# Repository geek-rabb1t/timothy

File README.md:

# Timothy

使いやすさを追求した左右分離型の自作キーボードキットです。
3Dプリント品のケースを採用することで市販品のような形状を実現しています。

キーボードキットや、半完成品は以下のサイトで販売しています。
カスタマイズしたり、ご自身で発注したい場合はこのリポジトリデータをご利用ください。

- キーボードキット：  
https://geek-rabb1t.booth.pm/items/4213539
- パームレスト：  
https://geek-rabb1t.booth.pm/items/4214631

## ディレクトリ構成

* case  
caseの3Dデータ
* doc  
ビルドガイド
* firmware  
ビルド済みのファームウェアや、各種設定データ
* gasket  
ガスケットのカッティングデータ
* palm-rest  
パームレストトップのカッティングデータ
* pcb
PCBのデータ
* plate  
スイッチプレートの外形データ

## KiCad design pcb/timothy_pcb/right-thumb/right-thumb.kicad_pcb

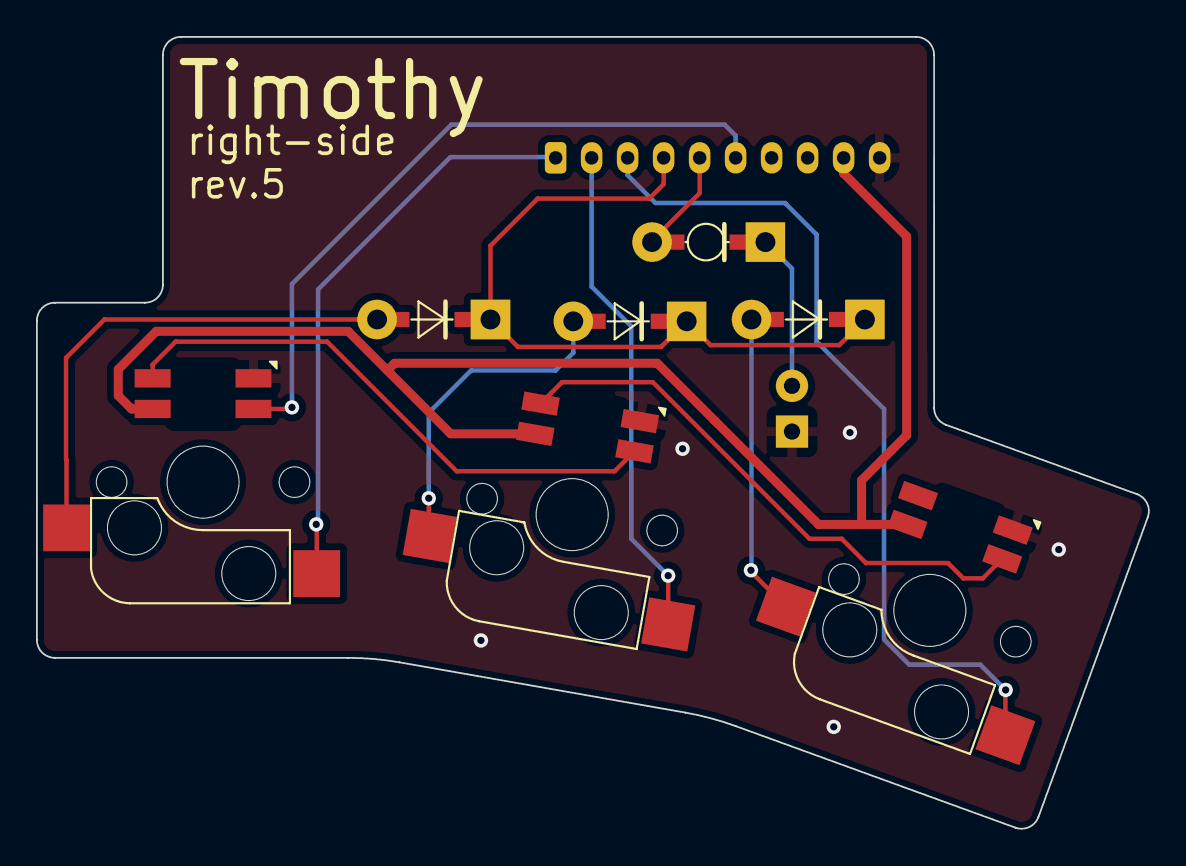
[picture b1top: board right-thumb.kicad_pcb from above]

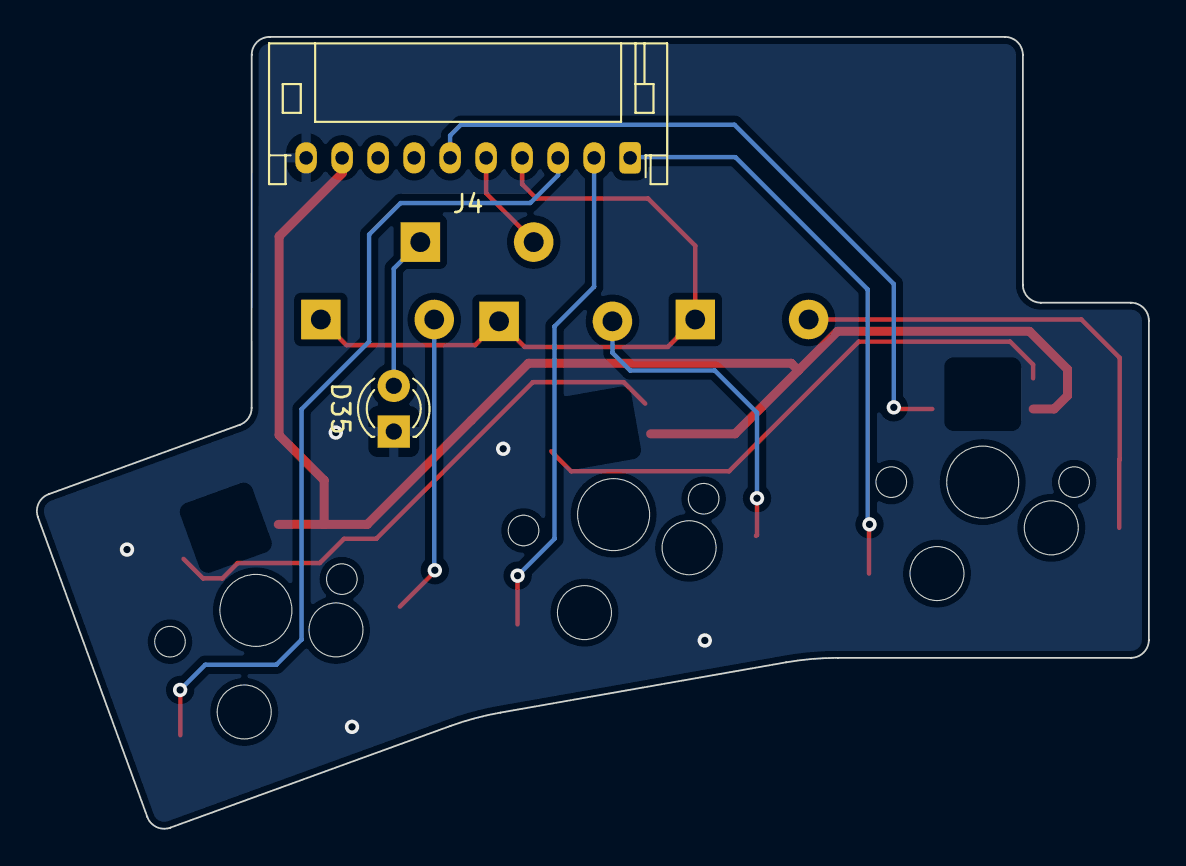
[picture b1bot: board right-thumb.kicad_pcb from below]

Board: 2 copper layers, 61.8 x 44.0 mm, 9 parts (2 on the bottom side), 14 nets.

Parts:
D35: LED; LED_D3.0mm
D36: CRD
D81, D82, D83: D; Diode
J4: Conn_01x10; JST_PH_S10B-PH-K_1x10_P2.00mm_Horizontal
SW68, SW69, SW70: Key_Switch_with_LED; MX_Socket_LED

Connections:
/BACKLIGHT_IN: J4.6, SW70.6 (DIN)
/C4: J4.1, SW70.1
/C5: J4.2, SW69.1
/C6: J4.3, SW68.1
/PWR_LED: D36.2 (A), J4.5
/R5: D81.1 (K), D82.1 (K), D83.1 (K), J4.4
/VCC: J4.9, SW68.3 (VDD), SW69.3 (VDD), SW70.3 (VDD)
GND: D35.1 (K), J4.10, SW68.5 (GND), SW69.5 (GND), SW70.5 (GND)
unnamed: D35.2 (A), D36.1 (K)
unnamed: D81.2 (A), SW68.2
unnamed: D82.2 (A), SW69.2
unnamed: D83.2 (A), SW70.2
unnamed: SW68.6 (DIN), SW69.4 (DOUT)
unnamed: SW69.6 (DIN), SW70.4 (DOUT)

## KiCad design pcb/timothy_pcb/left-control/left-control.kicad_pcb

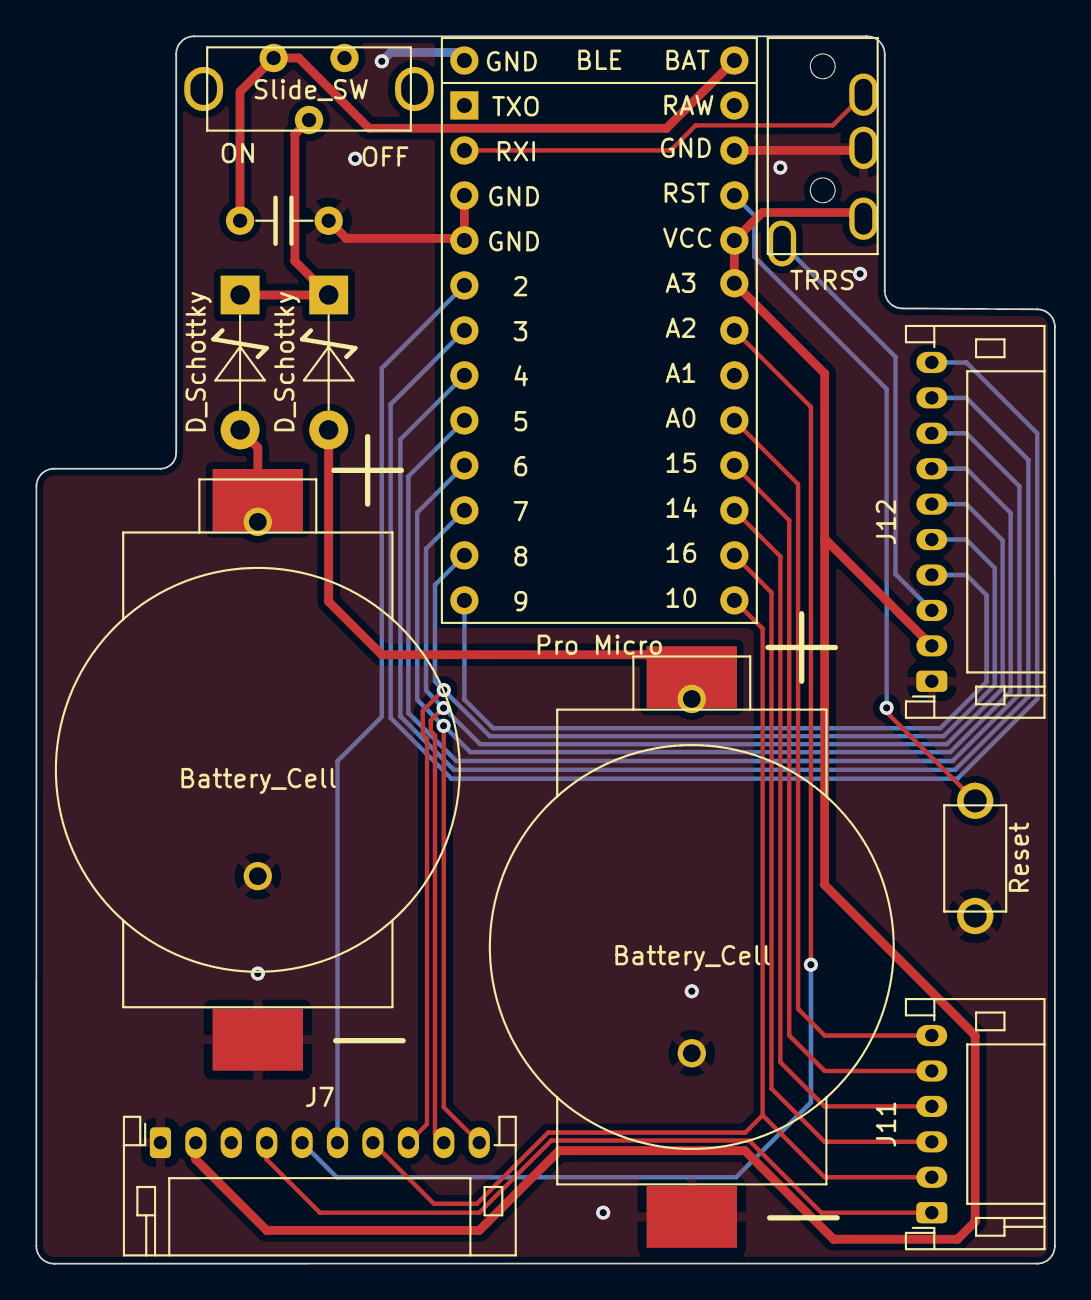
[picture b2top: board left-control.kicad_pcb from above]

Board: 2 copper layers, 57.5 x 69.3 mm, 12 parts (0 on the bottom side), 24 nets.

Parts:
BT1, BT2: Battery_Cell; CR2032_Holder_SMD
C1: 100μF; Capacitor
D70, D71: D_Schottky; Shottky_Barrier_Diode
J5: TRRS
J7: to_thumb; JST_PH_S10B-PH-K_1x10_P2.00mm_Horizontal
J11: control_to_main_1; JST_PH_S6B-PH-K_1x06_P2.00mm_Horizontal
J12: control_to_main_2; JST_PH_S10B-PH-K_1x10_P2.00mm_Horizontal
SW31: Slide_SW; Slide_Switch_ESD175202
SW63: Reset; Tactile_Switch
U1: Pro Micro; BLE_Micro_Pro

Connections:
/left_control/BACKLIGHT_TO_RIGHT: J5.4, J12.3
/left_control/BAT: C1.1, SW31.2 (B), U1.25 (BAT)
/left_control/C1: J12.10, U1.6 (PIN6)
/left_control/C2: J12.9, U1.7 (PIN7)
/left_control/C3: J12.8, U1.8 (PIN8)
/left_control/C4: J7.10, J12.7, U1.9 (PIN9)
/left_control/C5: J7.9, J12.6, U1.10 (PIN10)
/left_control/C6: J7.8, J12.5, U1.11 (PIN11)
/left_control/C7: J12.4, U1.12 (PIN12)
/left_control/FROM_THUMB_BACKLIGHT: J7.4, J11.1
/left_control/PWR_LED: J7.6, U1.5 (PIN5)
/left_control/R1: J11.6, U1.17 (PIN17)
/left_control/R2: J11.5, U1.16 (PIN16)
/left_control/R3: J11.4, U1.15 (PIN15)
/left_control/R4: J11.3, U1.14 (PIN14)
/left_control/R5: J7.7, J11.2, U1.13 (PIN13)
/left_control/SERIAL: J5.1, U1.2 (PIN2)
/left_control/TO_THUMB_BACKLIGHT: J7.5, U1.19 (PIN19)
/left_control/VCC: J5.3, J7.2, J12.2, U1.20 (PIN20), U1.21 (+4.3V)
GND: BT1.2 (-), BT2.2 (-), C1.2, J5.2, J7.1, J12.1, SW63.1, U1.0 (GND), U1.3 (GND), U1.4 (GND), U1.23 (GND)
unnamed: BT1.1 (+), D70.2 (A)
unnamed: BT2.1 (+), D71.2 (A)
unnamed: D70.1 (K), D71.1 (K), SW31.1 (A)
unnamed: SW63.2, U1.22 (BOOT(RST))

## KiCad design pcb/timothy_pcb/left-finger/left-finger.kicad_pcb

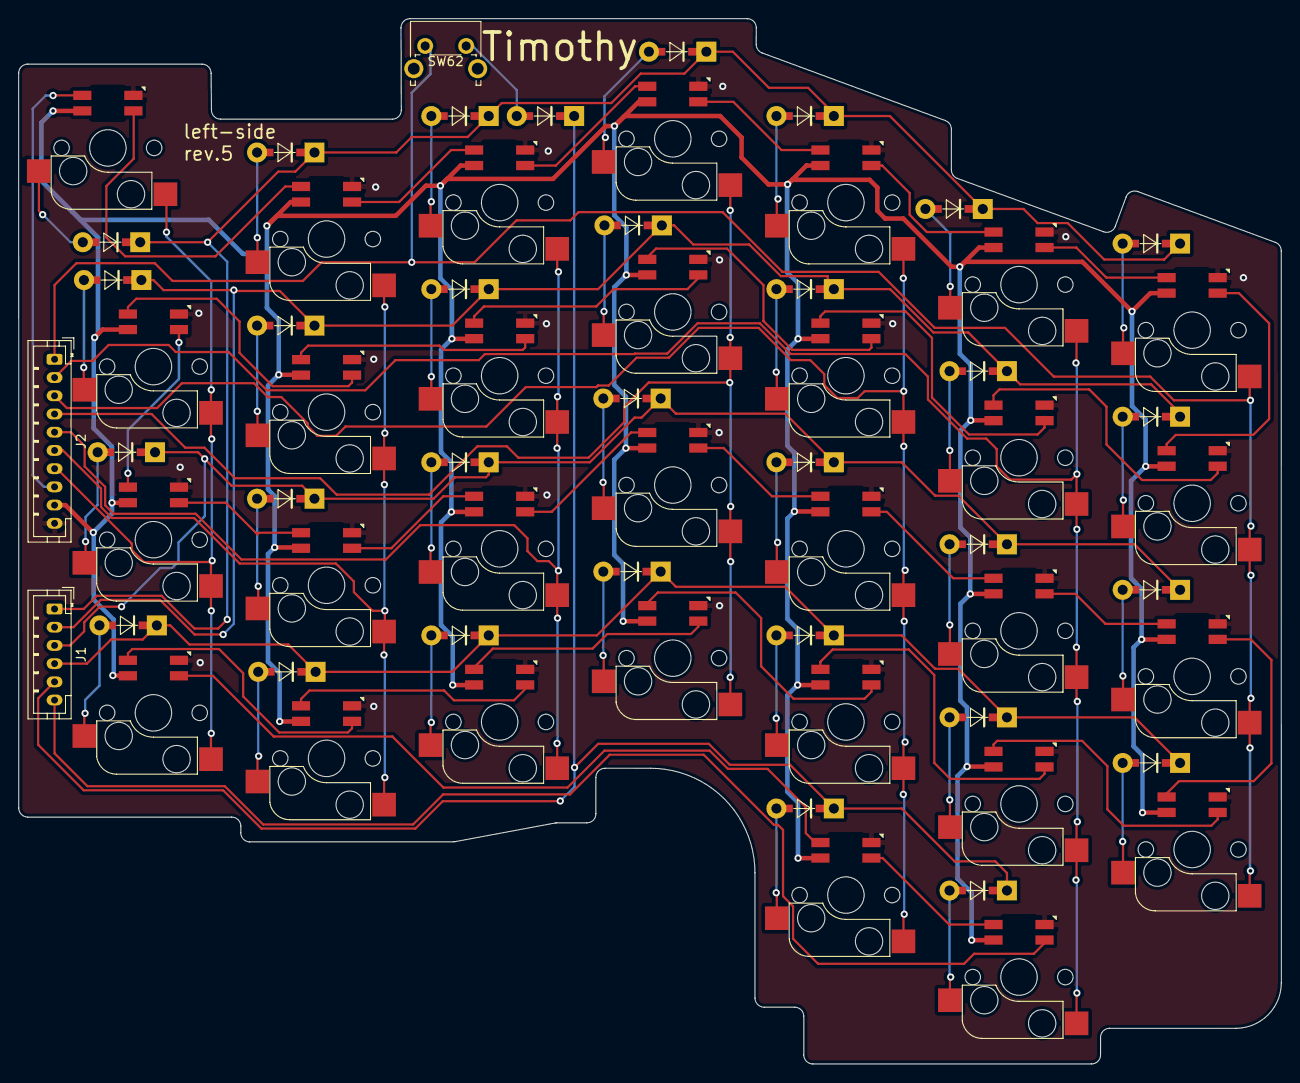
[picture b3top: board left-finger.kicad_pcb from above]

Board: 2 copper layers, 138.6 x 114.7 mm, 64 parts (0 on the bottom side), 76 nets.

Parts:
D1, D2, D3, D4, D5, D6, D7, D8, D9, D10, D11, D12, D13, D14, D15, D16, D17, D18, D19, D20, D21, D24, D25, D26, D27, D28, D29, D30, D31, D32, D84: D; Diode
J1: Conn_01x06; JST_PH_B6B-PH-K_1x06_P2.00mm_Vertical
J2: Conn_01x10; JST_PH_B10B-PH-K_1x10_P2.00mm_Vertical
SW1, SW2, SW3, SW4, SW5, SW6, SW7, SW8, SW9, SW10, SW11, SW12, SW13, SW14, SW15, SW16, SW17, SW18, SW19, SW20, SW21, SW22, SW23, SW24, SW25, SW26, SW27, SW28, SW29, SW30: Key_Switch_with_LED; MX_Socket_LED
SW62: SW_Push; SW_Tactile_SPST_Angled_PTS645Vx83-2LFS

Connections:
/BACKLIGHT_IN: J1.6, SW24.6 (DIN)
/BACKLIGHT_OUT: J2.8, SW1.4 (DOUT)
/C1: J2.1, SW27.1, SW28.1, SW29.1, SW30.1, SW62.1
/C2: J2.2, SW22.1, SW23.1, SW24.1, SW25.1, SW26.1
/C3: J2.3, SW17.1, SW18.1, SW19.1, SW20.1, SW21.1
/C4: J2.4, SW13.1, SW14.1, SW15.1, SW16.1
/C5: J2.5, SW9.1, SW10.1, SW11.1, SW12.1
/C6: J2.6, SW5.1, SW6.1, SW7.1, SW8.1
/C7: J2.7, SW1.1, SW2.1, SW3.1, SW4.1
/R1: D3.1 (K), D7.1 (K), D11.1 (K), D15.1 (K), D19.1 (K), D26.1 (K), D31.1 (K), J1.1
/R2: D1.1 (K), D5.1 (K), D9.1 (K), D13.1 (K), D17.1 (K), D24.1 (K), D29.1 (K), J1.2
/R3: D4.1 (K), D8.1 (K), D12.1 (K), D16.1 (K), D20.1 (K), D27.1 (K), D32.1 (K), J1.3
/R4: D2.1 (K), D6.1 (K), D10.1 (K), D14.1 (K), D18.1 (K), D25.1 (K), D30.1 (K), J1.4
/R5: D21.1 (K), D28.1 (K), D84.1 (K), J1.5
/VCC: J2.9, SW1.3 (VDD), SW2.3 (VDD), SW3.3 (VDD), SW4.3 (VDD), SW5.3 (VDD), SW6.3 (VDD), SW7.3 (VDD), SW8.3 (VDD), SW9.3 (VDD), SW10.3 (VDD), SW11.3 (VDD), SW12.3 (VDD), SW13.3 (VDD), SW14.3 (VDD), SW15.3 (VDD), SW16.3 (VDD), SW17.3 (VDD), SW18.3 (VDD), SW19.3 (VDD), SW20.3 (VDD), SW21.3 (VDD), SW22.3 (VDD), SW23.3 (VDD), SW24.3 (VDD), SW25.3 (VDD), SW26.3 (VDD), SW27.3 (VDD), SW28.3 (VDD), SW29.3 (VDD), SW30.3 (VDD)
GND: J2.10, SW1.5 (GND), SW2.5 (GND), SW3.5 (GND), SW4.5 (GND), SW5.5 (GND), SW6.5 (GND), SW7.5 (GND), SW8.5 (GND), SW9.5 (GND), SW10.5 (GND), SW11.5 (GND), SW12.5 (GND), SW13.5 (GND), SW14.5 (GND), SW15.5 (GND), SW16.5 (GND), SW17.5 (GND), SW18.5 (GND), SW19.5 (GND), SW20.5 (GND), SW21.5 (GND), SW22.5 (GND), SW23.5 (GND), SW24.5 (GND), SW25.5 (GND), SW26.5 (GND), SW27.5 (GND), SW28.5 (GND), SW29.5 (GND), SW30.5 (GND)
unnamed: D1.2 (A), SW3.2
unnamed: D2.2 (A), SW4.2
unnamed: D3.2 (A), SW1.2
unnamed: D4.2 (A), SW2.2
unnamed: D5.2 (A), SW7.2
unnamed: D6.2 (A), SW8.2
unnamed: D7.2 (A), SW5.2
unnamed: D8.2 (A), SW6.2
unnamed: D9.2 (A), SW11.2
unnamed: D10.2 (A), SW12.2
unnamed: D11.2 (A), SW9.2
unnamed: D12.2 (A), SW10.2
unnamed: D13.2 (A), SW15.2
unnamed: D14.2 (A), SW16.2
unnamed: D15.2 (A), SW13.2
unnamed: D16.2 (A), SW14.2
unnamed: D17.2 (A), SW20.2
unnamed: D18.2 (A), SW21.2
unnamed: D19.2 (A), SW17.2
unnamed: D20.2 (A), SW18.2
unnamed: D21.2 (A), SW19.2
unnamed: D24.2 (A), SW25.2
unnamed: D25.2 (A), SW26.2
unnamed: D26.2 (A), SW22.2
unnamed: D27.2 (A), SW23.2
unnamed: D28.2 (A), SW24.2
unnamed: D29.2 (A), SW29.2
unnamed: D30.2 (A), SW30.2
unnamed: D31.2 (A), SW27.2
unnamed: D32.2 (A), SW28.2
unnamed: D84.2 (A), SW62.2
unnamed: SW1.6 (DIN), SW5.4 (DOUT)
unnamed: SW2.4 (DOUT), SW3.6 (DIN)
unnamed: SW2.6 (DIN), SW6.4 (DOUT)
unnamed: SW3.4 (DOUT), SW7.6 (DIN)
unnamed: SW4.4 (DOUT), SW8.6 (DIN)
unnamed: SW5.6 (DIN), SW9.4 (DOUT)
unnamed: SW6.6 (DIN), SW10.4 (DOUT)
unnamed: SW10.6 (DIN), SW14.4 (DOUT)
unnamed: SW11.4 (DOUT), SW15.6 (DIN)
unnamed: SW7.4 (DOUT), SW11.6 (DIN)
unnamed: SW12.4 (DOUT), SW16.6 (DIN)
unnamed: SW8.4 (DOUT), SW12.6 (DIN)
unnamed: SW9.6 (DIN), SW13.4 (DOUT)
unnamed: SW13.6 (DIN), SW17.4 (DOUT)
unnamed: SW14.6 (DIN), SW18.4 (DOUT)
unnamed: SW15.4 (DOUT), SW20.6 (DIN)
unnamed: SW16.4 (DOUT), SW21.6 (DIN)
unnamed: SW17.6 (DIN), SW22.4 (DOUT)
unnamed: SW18.6 (DIN), SW23.4 (DOUT)
unnamed: SW4.6 (DIN), SW19.4 (DOUT)
unnamed: SW19.6 (DIN), SW24.4 (DOUT)
unnamed: SW20.4 (DOUT), SW25.6 (DIN)
unnamed: SW21.4 (DOUT), SW26.6 (DIN)
unnamed: SW22.6 (DIN), SW27.4 (DOUT)
unnamed: SW23.6 (DIN), SW28.4 (DOUT)
unnamed: SW25.4 (DOUT), SW29.6 (DIN)
unnamed: SW26.4 (DOUT), SW30.6 (DIN)
unnamed: SW27.6 (DIN), SW29.4 (DOUT)
unnamed: SW28.6 (DIN), SW30.4 (DOUT)

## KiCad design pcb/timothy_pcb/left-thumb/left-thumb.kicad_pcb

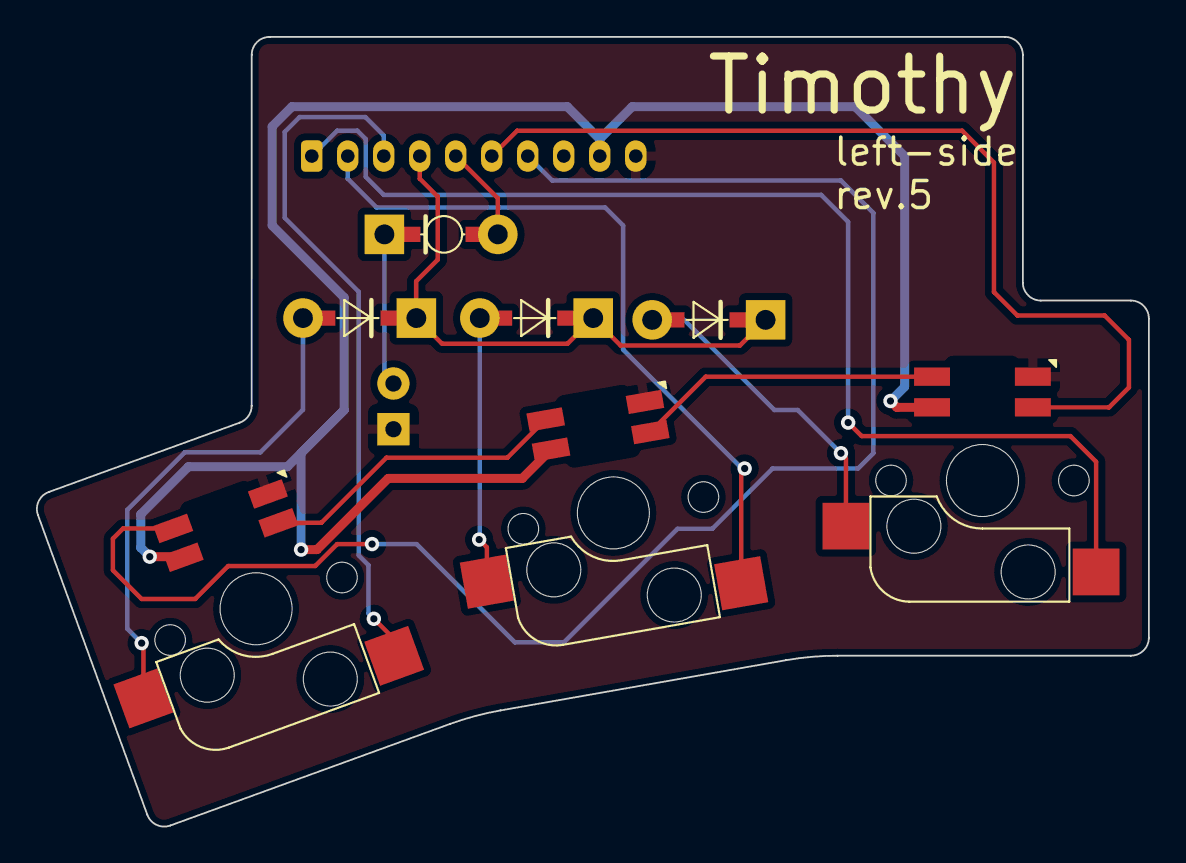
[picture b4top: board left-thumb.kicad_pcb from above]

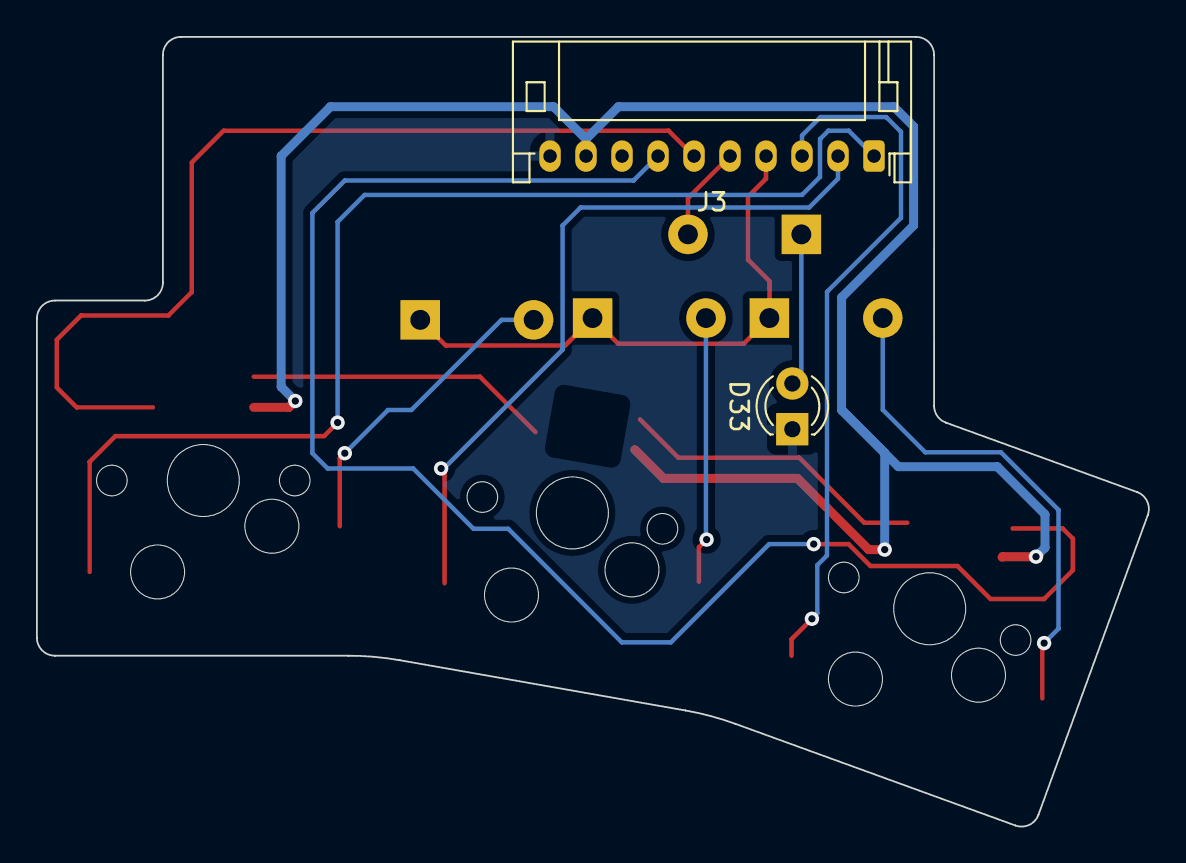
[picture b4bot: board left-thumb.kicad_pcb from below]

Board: 2 copper layers, 61.8 x 43.9 mm, 9 parts (2 on the bottom side), 14 nets.

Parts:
D33: LED; LED_D3.0mm
D34: CRD
D76, D77, D78: D; Diode
J3: Conn_01x10; JST_PH_S10B-PH-K_1x10_P2.00mm_Horizontal
SW64, SW65, SW66: Key_Switch_with_LED; MX_Socket_LED

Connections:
/BACKLIGHT_IN: J3.6, SW66.6 (DIN)
/BACKLIGHT_OUT: J3.7, SW64.4 (DOUT)
/C4: J3.1, SW66.1
/C5: J3.2, SW65.1
/C6: J3.3, SW64.1
/PWR_LED: D34.2, J3.5
/R5: D76.1 (K), D77.1 (K), D78.1 (K), J3.4
/VCC: J3.9, SW64.3 (VDD), SW65.3 (VDD), SW66.3 (VDD)
GND: D33.1 (K), J3.10, SW64.5 (GND), SW65.5 (GND), SW66.5 (GND)
unnamed: D76.2 (A), SW64.2
unnamed: D77.2 (A), SW65.2
unnamed: D78.2 (A), SW66.2
unnamed: SW64.6 (DIN), SW65.4 (DOUT)
unnamed: SW65.6 (DIN), SW66.4 (DOUT)

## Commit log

2022-12-24 add firmware
2022-12-24 add timothy_via.zip
2022-12-24 add setting.zip
2022-12-24 add buildguide
2022-12-24 Add images to build guide
2022-12-24 update images
